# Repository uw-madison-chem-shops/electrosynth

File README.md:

# electrosynth 

Inexpensive circuits made for multi-channel electrochemical synthesis.
Galvanosynth: constant current driver.
Electrosynth: constant potential driver.

## Repository

This is an open source hardware project licensed under the CERN Open Hardware Licence Version 2 - Permissive.
Please see the LICENSE file for the complete license.

This repository is being mirrored to several version control systems in an attempt to ensure maximum avaliability.

| name             | url                                                                  |
| ---------------- | -------------------------------------------------------------------- |
| blaise           | http://git.blaise.zone/uw-madison-chem-shops/electrosynth.git/about/ |
| Codeberg         | https://codeberg.org/uw-madison-chem-shops/electrosynth              |
| GitHub (primary) | https://github.com/uw-madison-chem-shops/electrosynth                |
| GitLab           | https://gitlab.com/uw-madison-chem-shops/electrosynth                |

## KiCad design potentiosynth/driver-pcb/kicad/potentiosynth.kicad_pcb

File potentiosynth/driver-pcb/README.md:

# potentiosynth driver-pcb

An inexpensive circuit made for driving multiple electrochemical constant potential reactions.

## PCB

This PCB was designed using [KiCAD](https://www.kicad.org/) version 5.
Refer to [potentiosynth.pdf](./potentiosynth.pdf) for schematic. 
PCB images generated with [tracespace](https://github.com/tracespace/tracespace) follow.

## Bill of Materials

| reference      | value         | manufacturer  | part number          | vendors | # Per Board |
| :------------- | :------------ | :------------ | :------------------- | :------ | :--------- |
| 3/8 ˝ Square Trimpot® Trimming Potentiometer | $3.00 | Bourns | 3296X-1-202LF | DigiKey | 8 |
| Low-power Operational Amplifier  | $2.00  | Texas Instruments | TLV9154IDR | DigiKey | 8 |
| Fuse Block  | $3.00  | Littelfuse | 01550900M | DigiKey | 1 |
| 1 Amp Fuse  | $2.00  | Littelfuse | 0451001.MRL | DigiKey | 1 |
| PC TEST POINT MULTIPURPOSE RED  | $0.50  | Keystone Electronics | 5010 | Newark | 1 |
| PC TEST POINT MULTIPURPOSE BLACK  | $0.50  | Keystone Electronics | 5011 | Newark | 1 |
| Barrel Jack - 2.1 mm  | $0.50  | CUI | PJ-002A | DigiKey | 2 |
| 1/4W 4x 1k Resistors - 1206 | :------ | :------------ | :-------------- | :------ | 8 |
| 1/4W 4x 100k Resistors - 1206 | :------ | :------------ | :-------------- | :------ | 8 |
| 100 nF Capacitor - 1206 | :------ | :------------ | :-------------- | :------ | 1 |
| 330 nF Capacitor - 1206 | :------ | :------------ | :-------------- | :------ | 1 |
| 100 uF Capacitor - 1206 | :------ | :------------ | :-------------- | :------ | 1 |
| 1 uF Capacitor - 1206 | :------ | :------------ | :-------------- | :------ | 8 |
| R-7B15 - 0.5 | :------ | :------------ | :-------------- | :------ | 1 |

All prices are extended.
PCB itself should cost around $5.

## Changelog

### Unprinted

### Revision C

Added
- capacitor makes error detection better when unloaded
- bipolar error detection

### Revision B

Changed
- added fuse

Fixed
- added buffer amplifier since the differential amplifier drew too much current from reference

### Revision A 

Changed
- initial design

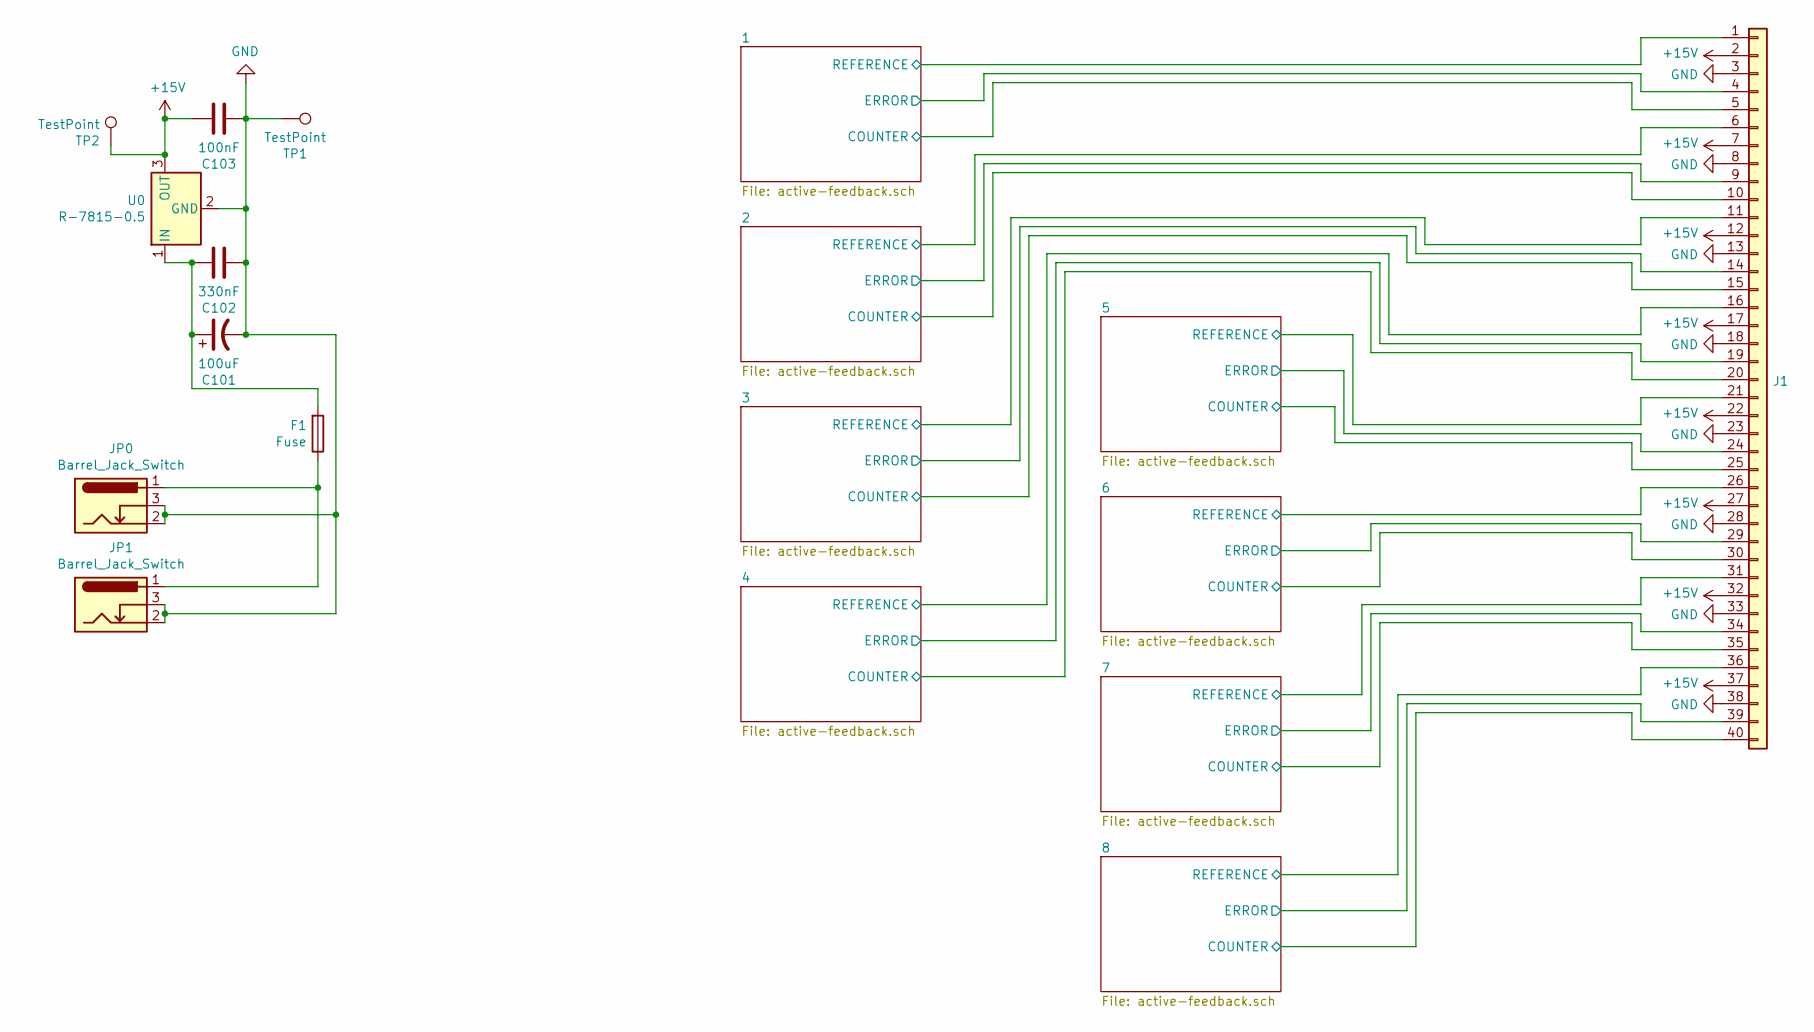
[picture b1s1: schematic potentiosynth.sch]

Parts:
C101: 100uF; CP_Radial_Tantal_D7.0mm_P2.50mm
C102: 330nF; C_1206_3216Metric_Pad1.33x1.80mm_HandSolder
C103: 100nF; C_1206_3216Metric_Pad1.33x1.80mm_HandSolder
F1: Fuse; 01550900M
J1: Conn_01x40; PinHeader_1x40_P2.54mm_Horizontal
JP0, JP1: Barrel_Jack_Switch; BarrelJack_Horizontal
TP1, TP2: TestPoint; TestPoint_THTPad_D3.0mm_Drill1.5mm
U0: R-7815-0.5; CONV_VXO7815-500-M

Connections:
+15V: C103.1, J1.2, J1.7, J1.12, J1.17, J1.22, J1.27, J1.32, J1.37, TP2.1, U0.3 (OUT); also elsewhere on the board
/1/COUNTER: J1.5; also elsewhere on the board
/1/ERROR: J1.4; also elsewhere on the board
/1/REFERENCE: J1.1; also elsewhere on the board
/2/COUNTER: J1.10; also elsewhere on the board
/2/ERROR: J1.9; also elsewhere on the board
/2/REFERENCE: J1.6; also elsewhere on the board
/3/COUNTER: J1.15; also elsewhere on the board
/3/ERROR: J1.14; also elsewhere on the board
/3/REFERENCE: J1.11; also elsewhere on the board
/4/COUNTER: J1.20; also elsewhere on the board
/4/ERROR: J1.19; also elsewhere on the board
/4/REFERENCE: J1.16; also elsewhere on the board
/5/COUNTER: J1.25; also elsewhere on the board
/5/ERROR: J1.24; also elsewhere on the board
/5/REFERENCE: J1.21; also elsewhere on the board
/6/COUNTER: J1.30; also elsewhere on the board
/6/ERROR: J1.29; also elsewhere on the board
/6/REFERENCE: J1.26; also elsewhere on the board
/7/COUNTER: J1.35; also elsewhere on the board
/7/ERROR: J1.34; also elsewhere on the board
/7/REFERENCE: J1.31; also elsewhere on the board
/8/COUNTER: J1.40; also elsewhere on the board
/8/ERROR: J1.39; also elsewhere on the board
/8/REFERENCE: J1.36; also elsewhere on the board
GND: C101.2, C102.2, C103.2, J1.3, J1.8, J1.13, J1.18, J1.23, J1.28, J1.33, J1.38, JP0.2, JP0.3, JP1.2, JP1.3, TP1.1, U0.2 (GND); also elsewhere on the board
unnamed: C101.1, C102.1, F1.2, U0.1 (IN)
unnamed: F1.1, JP0.1, JP1.1

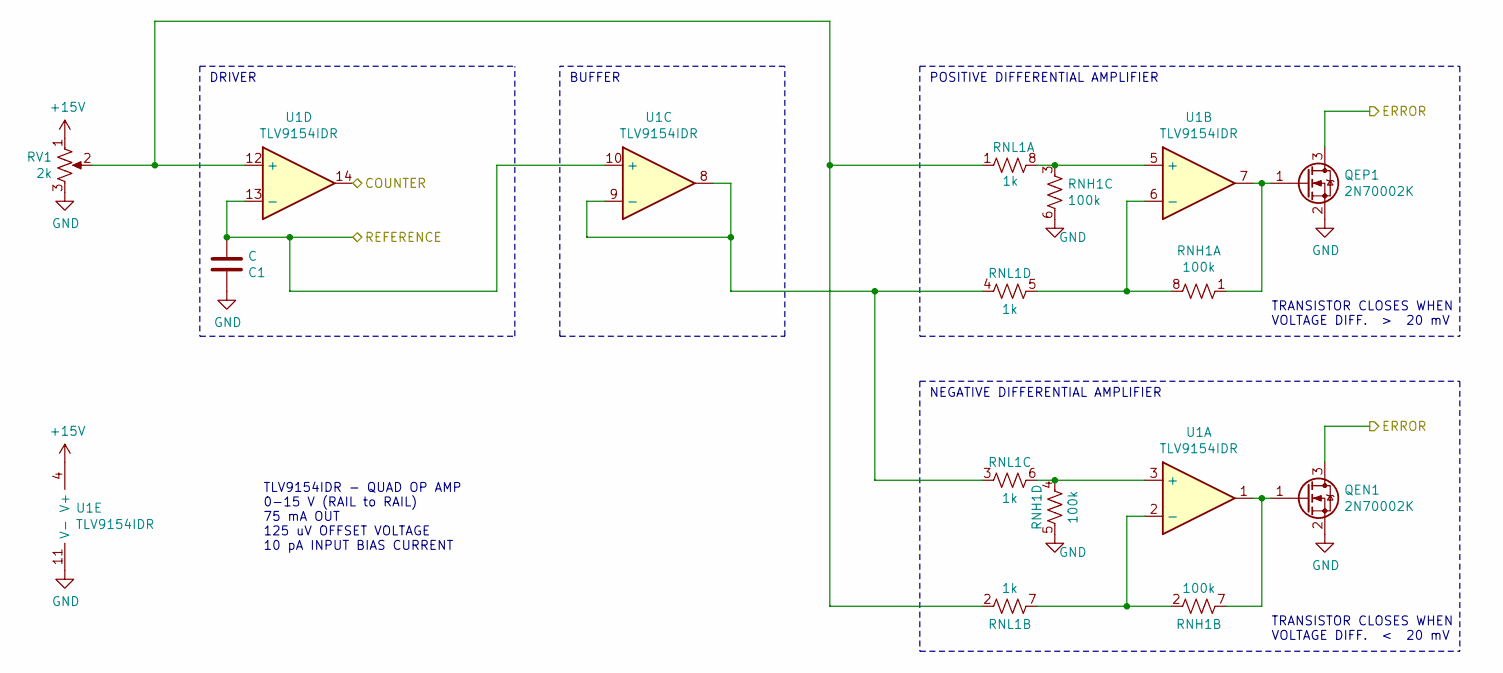
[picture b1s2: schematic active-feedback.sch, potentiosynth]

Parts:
C1: C; C_1206_3216Metric_Pad1.33x1.80mm_HandSolder
QEN1: 2N70002K; SOT-23_Handsoldering
QEP1: 2N70002K; SOT-23_Handsoldering
RNH1: 100k; CAY16-104J4LF
RNL1: 1k; CAY16-104J4LF
RV1: 2k; Potentiometer_Bourns_3296X_Horizontal
U1: TLV9154IDR; SOIC-14_3.9x8.7mm_P1.27mm

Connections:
+15V: RV1.1, U1.4 (V+); also elsewhere on the board
/1/COUNTER: U1.14; also elsewhere on the board
/1/ERROR: QEN1.3 (D), QEP1.3 (D); also elsewhere on the board
/1/REFERENCE: C1.1, U1.10 (+), U1.13 (-); also elsewhere on the board
GND: C1.2, QEN1.2 (S), QEP1.2 (S), RNH1.5 (R4.2), RNH1.6 (R3.2), RV1.3, U1.11 (V-); also elsewhere on the board
unnamed: QEN1.1 (G), RNH1.7 (R2.2), U1.1
unnamed: QEP1.1 (G), RNH1.1 (R1.1), U1.7
unnamed: RNH1.2 (R2.1), RNL1.7 (R2.2), U1.2 (-)
unnamed: RNH1.3 (R3.1), RNL1.8 (R1.2), U1.5 (+)
unnamed: RNH1.4 (R4.1), RNL1.6 (R3.2), U1.3 (+)
unnamed: RNH1.8 (R1.2), RNL1.5 (R4.2), U1.6 (-)
unnamed: RNL1.1 (R1.1), RNL1.2 (R2.1), RV1.2, U1.12 (+)
unnamed: RNL1.3 (R3.1), RNL1.4 (R4.1), U1.8, U1.9 (-)

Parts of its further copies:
C2, C3, C4, C5, C6, C7, C8: C; C_1206_3216Metric_Pad1.33x1.80mm_HandSolder
QEN2, QEN3, QEN4, QEN5, QEN6, QEN7, QEN8: 2N70002K; SOT-23_Handsoldering
QEP2, QEP3, QEP4, QEP5, QEP6, QEP7, QEP8: 2N70002K; SOT-23_Handsoldering
RNH2, RNH3, RNH4, RNH5, RNH6, RNH7, RNH8: 100k; CAY16-104J4LF
RNL2, RNL3, RNL4, RNL5, RNL6, RNL7, RNL8: 1k; CAY16-104J4LF
RV2, RV3, RV4, RV5, RV6, RV7, RV8: 2k; Potentiometer_Bourns_3296X_Horizontal
U2, U3, U4, U5, U6, U7, U8: TLV9154IDR; SOIC-14_3.9x8.7mm_P1.27mm

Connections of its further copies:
+15V: RV2.1, RV3.1, RV4.1, RV5.1, RV6.1, RV7.1, RV8.1, U2.4 (V+), U3.4 (V+), U4.4 (V+), U5.4 (V+), U6.4 (V+), U7.4 (V+), U8.4 (V+); also elsewhere on the board
/2/COUNTER: U2.14; also elsewhere on the board
/2/ERROR: QEN2.3 (D), QEP2.3 (D); also elsewhere on the board
/2/REFERENCE: C2.1, U2.10 (+), U2.13 (-); also elsewhere on the board
/3/COUNTER: U3.14; also elsewhere on the board
/3/ERROR: QEN3.3 (D), QEP3.3 (D); also elsewhere on the board
/3/REFERENCE: C3.1, U3.10 (+), U3.13 (-); also elsewhere on the board
/4/COUNTER: U4.14; also elsewhere on the board
/4/ERROR: QEN4.3 (D), QEP4.3 (D); also elsewhere on the board
/4/REFERENCE: C4.1, U4.10 (+), U4.13 (-); also elsewhere on the board
/5/COUNTER: U5.14; also elsewhere on the board
/5/ERROR: QEN5.3 (D), QEP5.3 (D); also elsewhere on the board
/5/REFERENCE: C5.1, U5.10 (+), U5.13 (-); also elsewhere on the board
/6/COUNTER: U6.14; also elsewhere on the board
/6/ERROR: QEN6.3 (D), QEP6.3 (D); also elsewhere on the board
/6/REFERENCE: C6.1, U6.10 (+), U6.13 (-); also elsewhere on the board
/7/COUNTER: U7.14; also elsewhere on the board
/7/ERROR: QEN7.3 (D), QEP7.3 (D); also elsewhere on the board
/7/REFERENCE: C7.1, U7.10 (+), U7.13 (-); also elsewhere on the board
/8/COUNTER: U8.14; also elsewhere on the board
/8/ERROR: QEN8.3 (D), QEP8.3 (D); also elsewhere on the board
/8/REFERENCE: C8.1, U8.10 (+), U8.13 (-); also elsewhere on the board
GND: C2.2, C3.2, C4.2, C5.2, C6.2, C7.2, C8.2, QEN2.2 (S), QEN3.2 (S), QEN4.2 (S), QEN5.2 (S), QEN6.2 (S), QEN7.2 (S), QEN8.2 (S), QEP2.2 (S), QEP3.2 (S), QEP4.2 (S), QEP5.2 (S), QEP6.2 (S), QEP7.2 (S), QEP8.2 (S), RNH2.5 (R4.2), RNH2.6 (R3.2), RNH3.5 (R4.2), RNH3.6 (R3.2), RNH4.5 (R4.2), RNH4.6 (R3.2), RNH5.5 (R4.2), RNH5.6 (R3.2), RNH6.5 (R4.2), RNH6.6 (R3.2), RNH7.5 (R4.2), RNH7.6 (R3.2), RNH8.5 (R4.2), RNH8.6 (R3.2), RV2.3, RV3.3, RV4.3, RV5.3, RV6.3, RV7.3, RV8.3, U2.11 (V-), U3.11 (V-), U4.11 (V-), U5.11 (V-), U6.11 (V-), U7.11 (V-), U8.11 (V-); also elsewhere on the board
unnamed: QEN2.1 (G), RNH2.7 (R2.2), U2.1
unnamed: QEN3.1 (G), RNH3.7 (R2.2), U3.1
unnamed: QEN4.1 (G), RNH4.7 (R2.2), U4.1
unnamed: QEN5.1 (G), RNH5.7 (R2.2), U5.1
unnamed: QEN6.1 (G), RNH6.7 (R2.2), U6.1
unnamed: QEN7.1 (G), RNH7.7 (R2.2), U7.1
unnamed: QEN8.1 (G), RNH8.7 (R2.2), U8.1
unnamed: QEP2.1 (G), RNH2.1 (R1.1), U2.7
unnamed: QEP3.1 (G), RNH3.1 (R1.1), U3.7
unnamed: QEP4.1 (G), RNH4.1 (R1.1), U4.7
unnamed: QEP5.1 (G), RNH5.1 (R1.1), U5.7
unnamed: QEP6.1 (G), RNH6.1 (R1.1), U6.7
unnamed: QEP7.1 (G), RNH7.1 (R1.1), U7.7
unnamed: QEP8.1 (G), RNH8.1 (R1.1), U8.7
unnamed: RNH2.2 (R2.1), RNL2.7 (R2.2), U2.2 (-)
unnamed: RNH2.3 (R3.1), RNL2.8 (R1.2), U2.5 (+)
unnamed: RNH2.4 (R4.1), RNL2.6 (R3.2), U2.3 (+)
unnamed: RNH2.8 (R1.2), RNL2.5 (R4.2), U2.6 (-)
unnamed: RNH3.2 (R2.1), RNL3.7 (R2.2), U3.2 (-)
unnamed: RNH3.3 (R3.1), RNL3.8 (R1.2), U3.5 (+)
unnamed: RNH3.4 (R4.1), RNL3.6 (R3.2), U3.3 (+)
unnamed: RNH3.8 (R1.2), RNL3.5 (R4.2), U3.6 (-)
unnamed: RNH4.2 (R2.1), RNL4.7 (R2.2), U4.2 (-)
unnamed: RNH4.3 (R3.1), RNL4.8 (R1.2), U4.5 (+)
unnamed: RNH4.4 (R4.1), RNL4.6 (R3.2), U4.3 (+)
unnamed: RNH4.8 (R1.2), RNL4.5 (R4.2), U4.6 (-)
unnamed: RNH5.2 (R2.1), RNL5.7 (R2.2), U5.2 (-)
unnamed: RNH5.3 (R3.1), RNL5.8 (R1.2), U5.5 (+)
unnamed: RNH5.4 (R4.1), RNL5.6 (R3.2), U5.3 (+)
unnamed: RNH5.8 (R1.2), RNL5.5 (R4.2), U5.6 (-)
unnamed: RNH6.2 (R2.1), RNL6.7 (R2.2), U6.2 (-)
unnamed: RNH6.3 (R3.1), RNL6.8 (R1.2), U6.5 (+)
unnamed: RNH6.4 (R4.1), RNL6.6 (R3.2), U6.3 (+)
unnamed: RNH6.8 (R1.2), RNL6.5 (R4.2), U6.6 (-)
unnamed: RNH7.2 (R2.1), RNL7.7 (R2.2), U7.2 (-)
unnamed: RNH7.3 (R3.1), RNL7.8 (R1.2), U7.5 (+)
unnamed: RNH7.4 (R4.1), RNL7.6 (R3.2), U7.3 (+)
unnamed: RNH7.8 (R1.2), RNL7.5 (R4.2), U7.6 (-)
unnamed: RNH8.2 (R2.1), RNL8.7 (R2.2), U8.2 (-)
unnamed: RNH8.3 (R3.1), RNL8.8 (R1.2), U8.5 (+)
unnamed: RNH8.4 (R4.1), RNL8.6 (R3.2), U8.3 (+)
unnamed: RNH8.8 (R1.2), RNL8.5 (R4.2), U8.6 (-)
unnamed: RNL2.1 (R1.1), RNL2.2 (R2.1), RV2.2, U2.12 (+)
unnamed: RNL2.3 (R3.1), RNL2.4 (R4.1), U2.8, U2.9 (-)
unnamed: RNL3.1 (R1.1), RNL3.2 (R2.1), RV3.2, U3.12 (+)
unnamed: RNL3.3 (R3.1), RNL3.4 (R4.1), U3.8, U3.9 (-)
unnamed: RNL4.1 (R1.1), RNL4.2 (R2.1), RV4.2, U4.12 (+)
unnamed: RNL4.3 (R3.1), RNL4.4 (R4.1), U4.8, U4.9 (-)
unnamed: RNL5.1 (R1.1), RNL5.2 (R2.1), RV5.2, U5.12 (+)
unnamed: RNL5.3 (R3.1), RNL5.4 (R4.1), U5.8, U5.9 (-)
unnamed: RNL6.1 (R1.1), RNL6.2 (R2.1), RV6.2, U6.12 (+)
unnamed: RNL6.3 (R3.1), RNL6.4 (R4.1), U6.8, U6.9 (-)
unnamed: RNL7.1 (R1.1), RNL7.2 (R2.1), RV7.2, U7.12 (+)
unnamed: RNL7.3 (R3.1), RNL7.4 (R4.1), U7.8, U7.9 (-)
unnamed: RNL8.1 (R1.1), RNL8.2 (R2.1), RV8.2, U8.12 (+)
unnamed: RNL8.3 (R3.1), RNL8.4 (R4.1), U8.8, U8.9 (-)

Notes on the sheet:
TRANSISTOR CLOSES WHEN VOLTAGE DIFF. > 20 mV
POSITIVE DIFFERENTIAL AMPLIFIER
BUFFER
DRIVER
TLV9154IDR - QUAD OP AMP 0-15 V (RAIL to RAIL) 75 mA OUT 125 uV OFFSET VOLTAGE 10 pA INPUT BIAS CURRENT
TRANSISTOR CLOSES WHEN VOLTAGE DIFF. < 20 mV
NEGATIVE DIFFERENTIAL AMPLIFIER

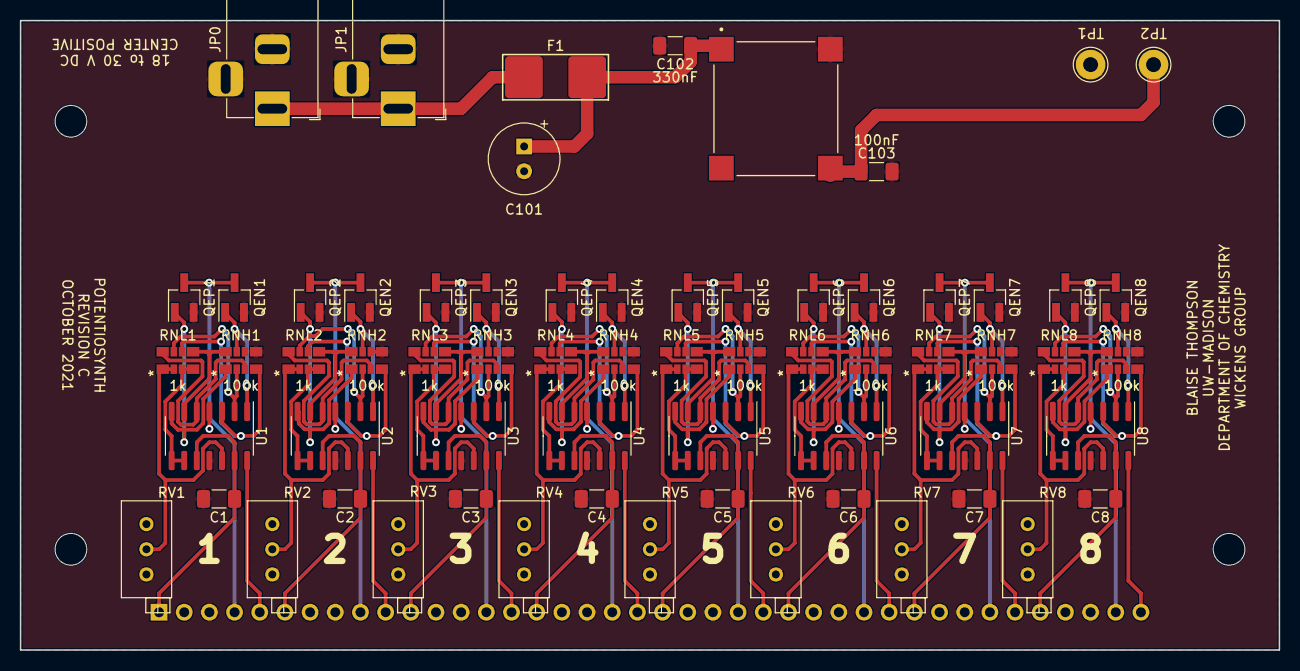
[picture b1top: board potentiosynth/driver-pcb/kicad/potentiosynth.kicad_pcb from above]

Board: 2 copper layers, 127.0 x 63.5 mm, 66 parts (1 on the bottom side), 92 nets.

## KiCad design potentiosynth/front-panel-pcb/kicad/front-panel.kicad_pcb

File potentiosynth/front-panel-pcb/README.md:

# potentiosynth front-panel-pcb

An inexpensive circuit made for driving multiple electrochemical constant potential reactions.

## PCB

This PCB was designed using [KiCAD](https://www.kicad.org/) version 5.
Refer to [front-panel.pdf](./front-panel.pdf) for schematic. 
PCB images generated with [tracespace](https://github.com/tracespace/tracespace) follow.

## Bill of Materials

| reference      | value         | manufacturer  | part number          | vendors | # per Board |
| :------------- | :------------ | :------------ | :------------------- | :------ | :----------  |
| Banana Jack Board Mount | $1.00 | Keystone Electronics | 575-4 | Newark | 24 |
| 40 Pin Header, Male, Right Angle | $0.00 | 3M | 2340-5111TG | N/A | 1 (Cut down to 3 pins)  |
| 0.1" Jumper - 2 Position | $0.00 | Multicomp | MC-2228CG | N/A | 1 |
| 1/4W 1k Resistors - 1206 | :----- | :------------ | :-------- | :------ | 11 |
| SMT LEDs - 1206 | :----- | :------------ | :-------- | :------ | 11  |

All prices are extended.
PCB itself should cost around $5.

## Changelog

### Unprinted

## Fixed
- fixed silkscreen labels for oxidation and reduction

### Revision A 

## Changed
- initial design

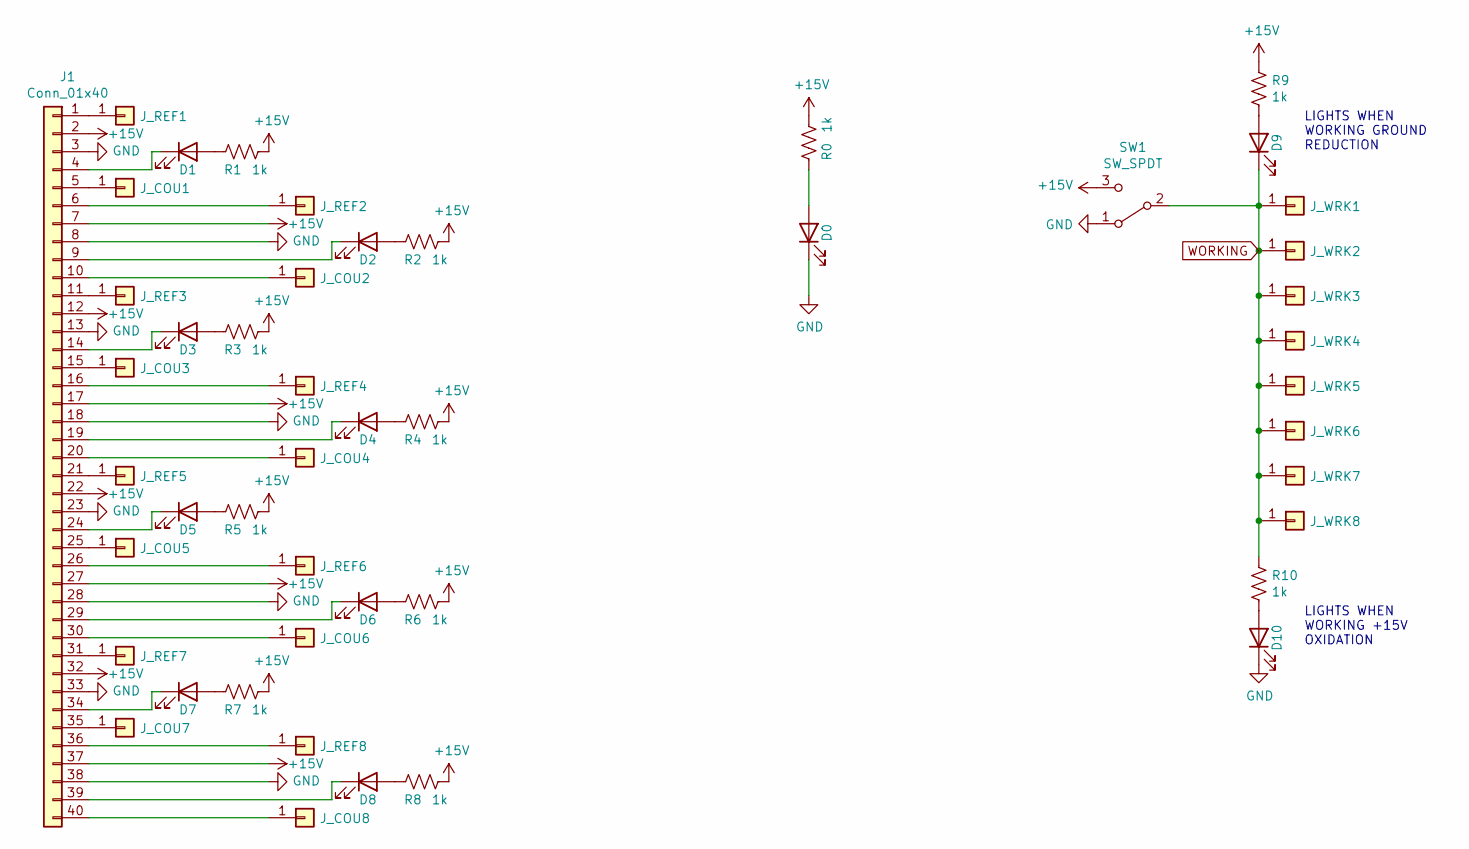
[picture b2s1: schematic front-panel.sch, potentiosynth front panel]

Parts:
D0, D1, D2, D3, D4, D5, D6, D7, D8, D9, D10: LED; D_1206_3216Metric
J1: Conn_01x40; PinHeader_1x40_P2.54mm_Vertical
J_COU1, J_COU2, J_COU3, J_COU4, J_COU5, J_COU6, J_COU7, J_COU8: Conn_01x01; Banana_Jack_1Pin
J_REF1, J_REF2, J_REF3, J_REF4, J_REF5, J_REF6, J_REF7, J_REF8: Conn_01x01; Banana_Jack_1Pin
J_WRK1, J_WRK2, J_WRK3, J_WRK4, J_WRK5, J_WRK6, J_WRK7, J_WRK8: Conn_01x01; Banana_Jack_1Pin
R0, R1, R2, R3, R4, R5, R6, R7, R8, R9, R10: 1k; R_1206_3216Metric
SW1: SW_SPDT; PinHeader_1x03_P2.54mm_Horizontal

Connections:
+15V: J1.2, J1.7, J1.12, J1.17, J1.22, J1.27, J1.32, J1.37, R0.1, R1.1, R2.1, R3.1, R4.1, R5.1, R6.1, R7.1, R8.1, R9.1, SW1.3 (C)
GND: D0.1 (K), D10.1 (K), J1.3, J1.8, J1.13, J1.18, J1.23, J1.28, J1.33, J1.38, SW1.1 (A)
unnamed: D0.2 (A), R0.2
unnamed: D1.1 (K), J1.4
unnamed: D1.2 (A), R1.2
unnamed: D2.1 (K), J1.9
unnamed: D2.2 (A), R2.2
unnamed: D3.1 (K), J1.14
unnamed: D3.2 (A), R3.2
unnamed: D4.1 (K), J1.19
unnamed: D4.2 (A), R4.2
unnamed: D5.1 (K), J1.24
unnamed: D5.2 (A), R5.2
unnamed: D6.1 (K), J1.29
unnamed: D6.2 (A), R6.2
unnamed: D7.1 (K), J1.34
unnamed: D7.2 (A), R7.2
unnamed: D8.1 (K), J1.39
unnamed: D8.2 (A), R8.2
unnamed: D9.2 (A), R9.2
unnamed: D10.2 (A), R10.2
unnamed: J1.1, J_REF1.1
unnamed: J1.5, J_COU1.1
unnamed: J1.6, J_REF2.1
unnamed: J1.10, J_COU2.1
unnamed: J1.11, J_REF3.1
unnamed: J1.15, J_COU3.1
unnamed: J1.16, J_REF4.1
unnamed: J1.20, J_COU4.1
unnamed: J1.21, J_REF5.1
unnamed: J1.25, J_COU5.1
unnamed: J1.26, J_REF6.1
unnamed: J1.30, J_COU6.1
unnamed: J1.31, J_REF7.1
unnamed: J1.35, J_COU7.1
unnamed: J1.36, J_REF8.1
unnamed: J1.40, J_COU8.1
WORKING: D9.1 (K), J_WRK1.1, J_WRK2.1, J_WRK3.1, J_WRK4.1, J_WRK5.1, J_WRK6.1, J_WRK7.1, J_WRK8.1, R10.1, SW1.2 (B)

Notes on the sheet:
LIGHTS WHEN WORKING GROUND REDUCTION
LIGHTS WHEN WORKING +15V OXIDATION

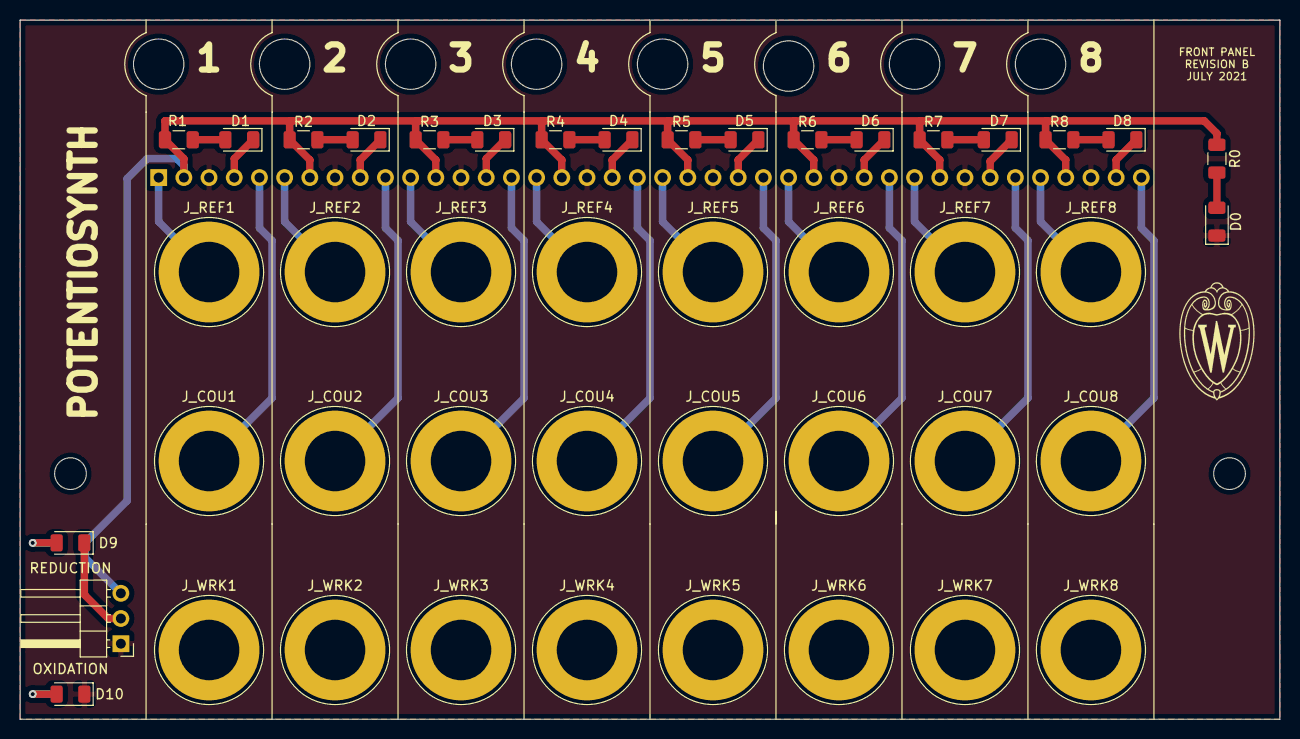
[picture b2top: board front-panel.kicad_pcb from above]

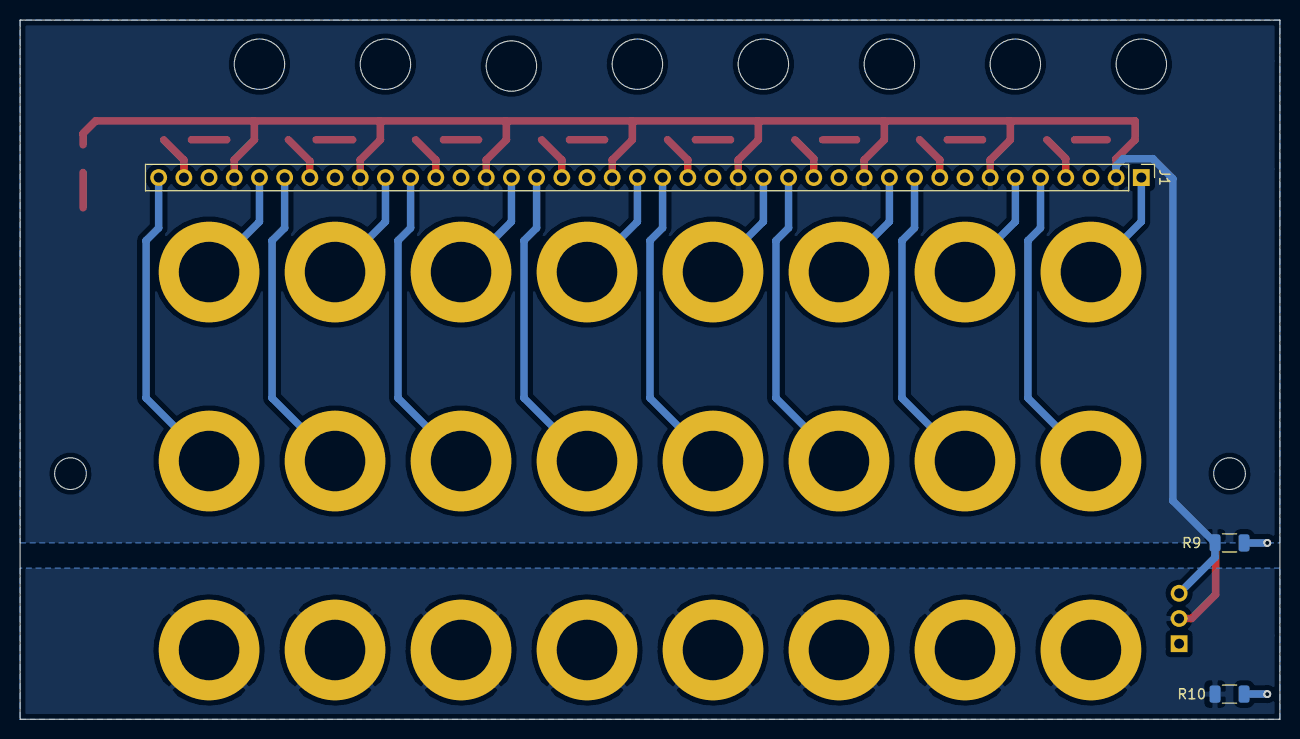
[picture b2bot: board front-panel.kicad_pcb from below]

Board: 2 copper layers, 127.0 x 70.5 mm, 48 parts (3 on the bottom side), 38 nets.

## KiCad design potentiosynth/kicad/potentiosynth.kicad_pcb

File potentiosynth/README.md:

# potentiosynth 

An inexpensive circuit made for driving multiple electrochemical constant potential reactions.

Each potentiosynth is made of three custom components:

- the main driver PCB
- the front panel PCB
- 3D printed bracket

See subdirectories for detailed instructions on each of these components.

## Bill of Materials

| reference      | value         | manufacturer  | part number          | vendors | # per Board |
| :------------- | :------------ | :------------ | :------------------- | :------ | :----------  |
| 40 Pin Header, Male, Right Angle | $0.00 | 3M | 2340-5111TG | Newark | 1 |
| 2" Standoff | $1.75 | Keystone Electronics | :------ | Newark | 4 |
| 0.625" Standoff | $0.50 | Keystone Electronics | :------ | Newark | 4 |

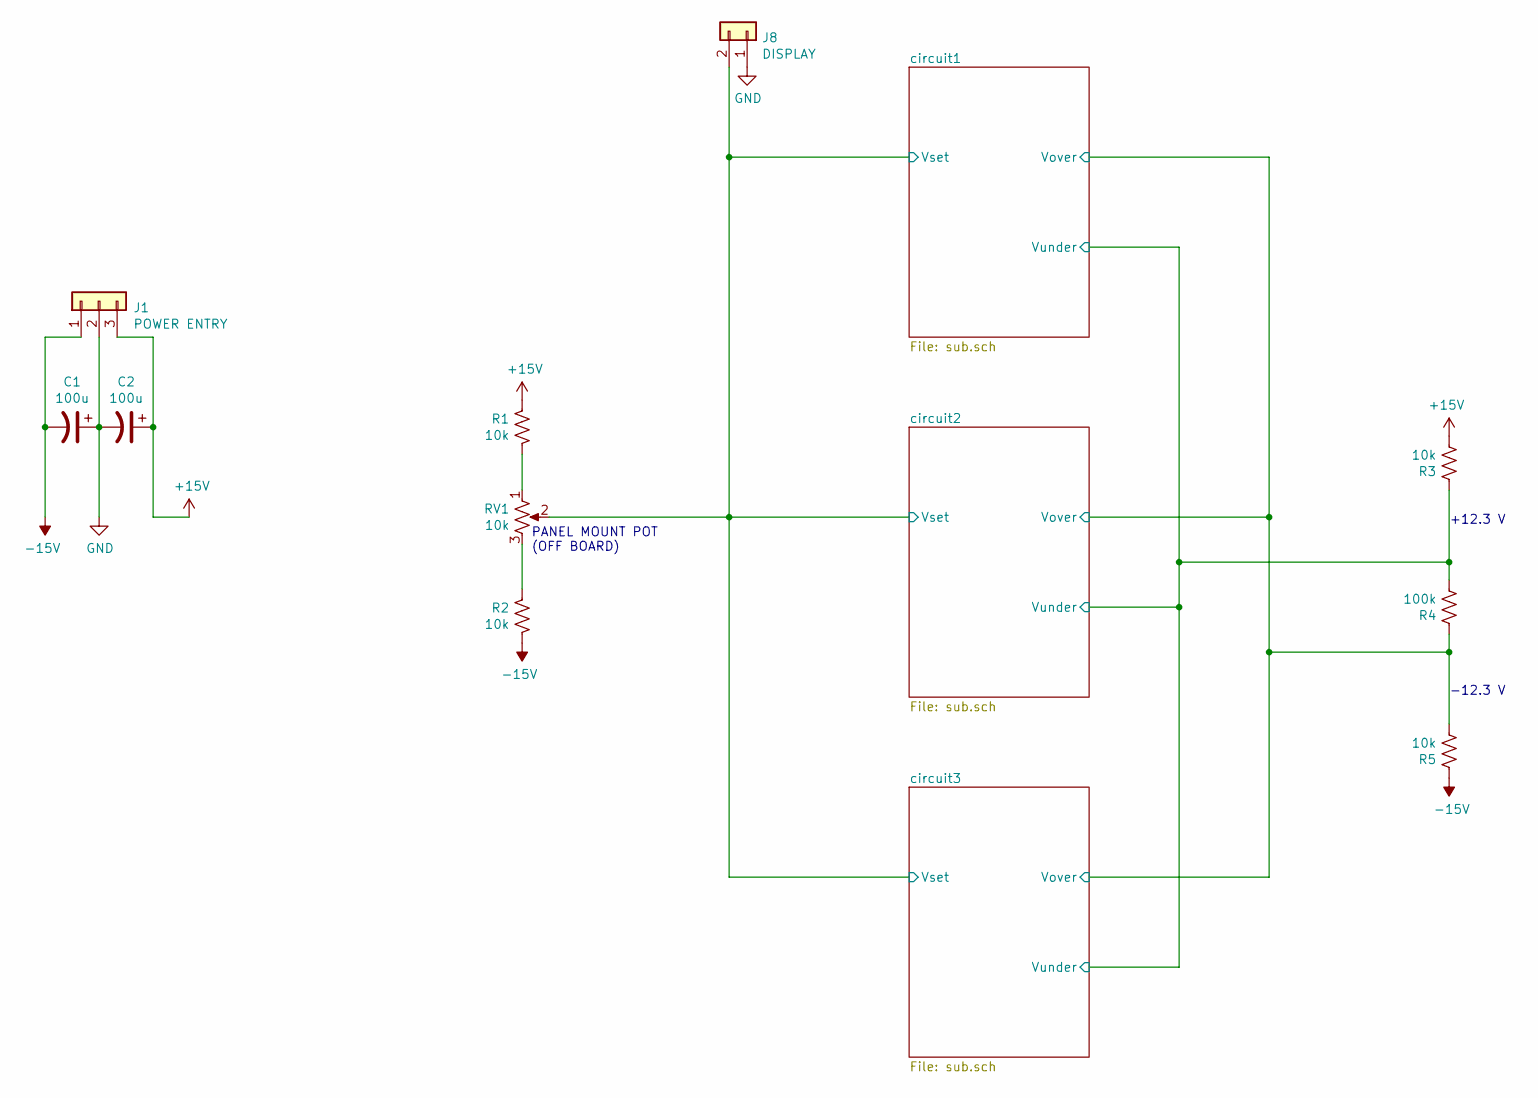
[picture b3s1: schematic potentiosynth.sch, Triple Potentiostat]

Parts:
C1, C2: 100u; CP_Radial_D7.5mm_P2.50mm
J1: POWER ENTRY; Molex_KK-254_AE-6410-03A_1x03_P2.54mm_Vertical
J8: DISPLAY; Molex_KK-254_AE-6410-02A_1x02_P2.54mm_Vertical
R1, R2, R3, R5: 10k; R_Axial_DIN0207_L6.3mm_D2.5mm_P7.62mm_Horizontal
R4: 100k; R_Axial_DIN0207_L6.3mm_D2.5mm_P7.62mm_Horizontal
RV1: 10k; Molex_KK-254_AE-6410-03A_1x03_P2.54mm_Vertical

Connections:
+15V: C2.1, J1.3, R1.2, R3.1; also elsewhere on the board
-15V: C1.2, J1.1, R2.1, R5.2; also elsewhere on the board
/circuit1/Vover: R4.2, R5.1; also elsewhere on the board
/circuit1/Vset: J8.2, RV1.2; also elsewhere on the board
/circuit1/Vunder: R3.2, R4.1; also elsewhere on the board
GND: C1.1, C2.2, J1.2, J8.1; also elsewhere on the board
unnamed: R1.1, RV1.1
unnamed: R2.2, RV1.3

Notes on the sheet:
PANEL MOUNT POT (OFF BOARD)
-12.3 V
+12.3 V

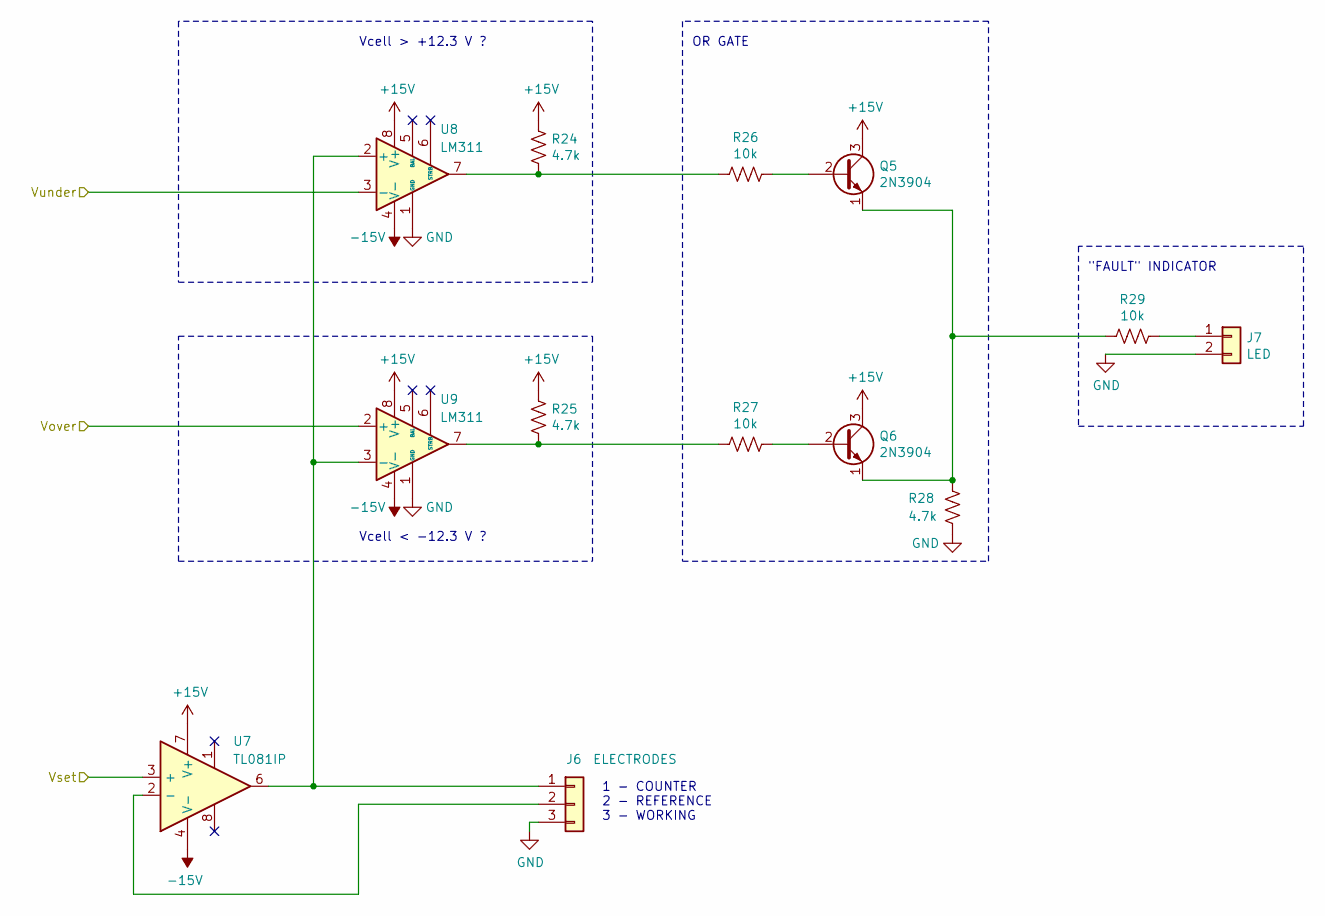
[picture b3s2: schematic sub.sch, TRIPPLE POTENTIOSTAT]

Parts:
J2: ELECTRODES; Molex_KK-254_AE-6410-03A_1x03_P2.54mm_Vertical
J3: LED; Molex_KK-254_AE-6410-02A_1x02_P2.54mm_Vertical
Q1, Q2: 2N3904; TO-92_Inline
R6, R7, R10: 4.7k; R_Axial_DIN0207_L6.3mm_D2.5mm_P7.62mm_Horizontal
R8, R9, R11: 10k; R_Axial_DIN0207_L6.3mm_D2.5mm_P7.62mm_Horizontal
U1: TL081IP; DIP-8_W7.62mm_Socket_LongPads
U2, U3: LM311; DIP-8_W7.62mm_Socket_LongPads

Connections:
+15V: Q1.3 (C), Q2.3 (C), R6.2, R7.1, U1.7 (V+), U2.8 (V+), U3.8 (V+); also elsewhere on the board
-15V: U1.4 (V-), U2.4 (V-), U3.4 (V-); also elsewhere on the board
/circuit1/Vover: U3.2 (+); also elsewhere on the board
/circuit1/Vset: U1.3 (+); also elsewhere on the board
/circuit1/Vunder: U2.3 (-); also elsewhere on the board
GND: J2.3, J3.2, R10.2, U2.1 (GND), U3.1 (GND); also elsewhere on the board
unnamed: J2.1, U1.6, U2.2 (+), U3.3 (-)
unnamed: J2.2, U1.2 (-)
unnamed: J3.1, R11.2
unnamed: Q1.1 (E), Q2.1 (E), R10.1, R11.1
unnamed: Q1.2 (B), R8.2
unnamed: Q2.2 (B), R9.2
unnamed: R6.1, R8.1, U2.7
unnamed: R7.2, R9.1, U3.7

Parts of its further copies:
J4, J6: ELECTRODES; Molex_KK-254_AE-6410-03A_1x03_P2.54mm_Vertical
J5, J7: LED; Molex_KK-254_AE-6410-02A_1x02_P2.54mm_Vertical
Q3, Q4, Q5, Q6: 2N3904; TO-92_Inline
R15, R16, R19, R24, R25, R28: 4.7k; R_Axial_DIN0207_L6.3mm_D2.5mm_P7.62mm_Horizontal
R17, R18, R20, R26, R27, R29: 10k; R_Axial_DIN0207_L6.3mm_D2.5mm_P7.62mm_Horizontal
U5, U6, U8, U9: LM311; DIP-8_W7.62mm_Socket_LongPads

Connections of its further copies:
+15V: Q3.3 (C), Q4.3 (C), Q5.3 (C), Q6.3 (C), R15.2, R16.1, R24.2, R25.1, U5.8 (V+), U6.8 (V+), U8.8 (V+), U9.8 (V+); also elsewhere on the board
-15V: U5.4 (V-), U6.4 (V-), U8.4 (V-), U9.4 (V-); also elsewhere on the board
/circuit1/Vover: U6.2 (+), U9.2 (+); also elsewhere on the board
/circuit1/Vunder: U5.3 (-), U8.3 (-); also elsewhere on the board
GND: J4.3, J5.2, J6.3, J7.2, R19.2, R28.2, U5.1 (GND), U6.1 (GND), U8.1 (GND), U9.1 (GND); also elsewhere on the board
unnamed 9: J4.1, U5.2 (+), U6.3 (-); also elsewhere on the board
unnamed 10: J4.2; also elsewhere on the board
unnamed: J5.1, R20.2
unnamed 12: J6.1, U8.2 (+), U9.3 (-); also elsewhere on the board
unnamed 13: J6.2; also elsewhere on the board
unnamed: J7.1, R29.2
unnamed: Q3.1 (E), Q4.1 (E), R19.1, R20.1
unnamed: Q3.2 (B), R17.2
unnamed: Q4.2 (B), R18.2
unnamed: Q5.1 (E), Q6.1 (E), R28.1, R29.1
unnamed: Q5.2 (B), R26.2
unnamed: Q6.2 (B), R27.2
unnamed: R15.1, R17.1, U5.7
unnamed: R16.2, R18.1, U6.7
unnamed: R24.1, R26.1, U8.7
unnamed: R25.2, R27.1, U9.7

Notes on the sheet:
1 - COUNTER 2 - REFERENCE 3 - WORKING
Vcell < -12.3 V ?
Vcell > +12.3 V ?
OR GATE
"FAULT" INDICATOR

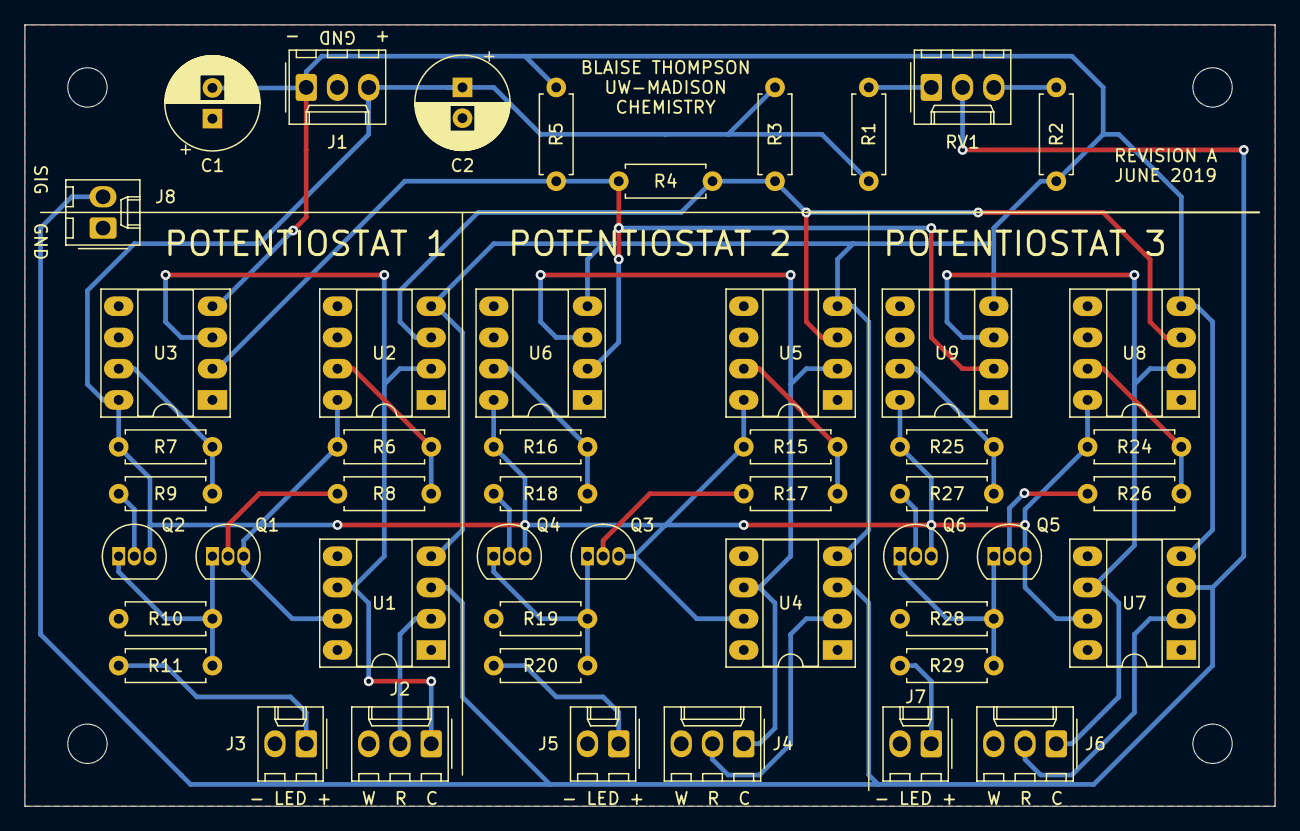
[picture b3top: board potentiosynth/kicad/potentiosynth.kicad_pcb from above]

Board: 2 copper layers, 101.6 x 63.5 mm, 49 parts (0 on the bottom side), 32 nets.

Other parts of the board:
U4, U7: OP27GPZ; DIP-8_W7.62mm_Socket_LongPads

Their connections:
+15V: U4.7, U7.7; also elsewhere on the board
-15V: U4.4, U7.4; also elsewhere on the board
/circuit1/Vset: U4.3, U7.3; also elsewhere on the board
unnamed 9: U4.6; also elsewhere on the board
unnamed 10: U4.2; also elsewhere on the board
unnamed 12: U7.6; also elsewhere on the board
unnamed 13: U7.2; also elsewhere on the board

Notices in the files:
parts and their libraries:
Copyright 2021 Accelerated Designs. All rights reserved.
